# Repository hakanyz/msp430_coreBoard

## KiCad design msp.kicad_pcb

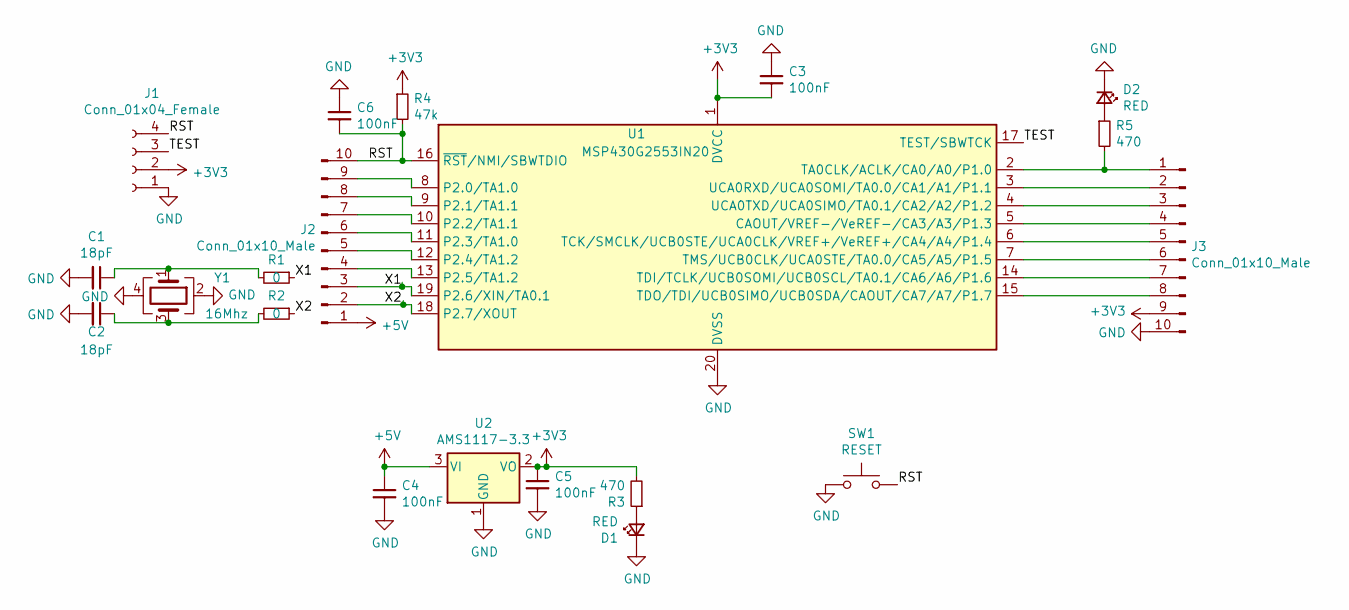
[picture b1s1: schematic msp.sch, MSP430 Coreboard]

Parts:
C1, C2: 18pF; C_0805_2012Metric
C3, C4, C5, C6: 100nF; C_0805_2012Metric
D1, D2: RED; LED_0805_2012Metric
J1: Conn_01x04_Female; PinSocket_1x04_P2.54mm_Vertical
J2, J3: Conn_01x10_Male; PinSocket_1x10_P2.54mm_Vertical
R1, R2: 0; R_0805_2012Metric
R3, R5: 470; R_0805_2012Metric
R4: 47k; R_0805_2012Metric
SW1: RESET; SW_Push_1P1T_NO_6x6mm_H9.5mm
U1: MSP430G2553IN20; TSSOP-20_4.4x6.5mm_P0.65mm
U2: AMS1117-3.3; SOT-223-3_TabPin2
Y1: 16Mhz; Crystal_SMD_3225-4Pin_3.2x2.5mm

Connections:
+3V3: C3.2, C5.1, J1.2, J3.9, R3.2, R4.1, U1.1 (DVCC), U2.2 (VO)
+5V: C4.1, J2.1, U2.3 (VI)
/RST: C6.2, J1.4, J2.10, R4.2, SW1.2, U1.16 (~RST~/NMI/SBWTDIO); also elsewhere on the board
/TEST: J1.3, U1.17 (TEST/SBWTCK)
/X1: J2.3, R1.1, U1.19 (P2.6/XIN/TA0.1)
/X2: J2.2, R2.1, U1.18 (P2.7/XOUT)
GND: C1.2, C2.2, C3.1, C4.2, C5.2, C6.1, D1.1 (K), D2.1 (K), J1.1, J3.10, SW1.1, U1.20 (DVSS), U2.1 (GND), Y1.2, Y1.4; also elsewhere on the board
unnamed: C1.1, R1.2, Y1.1
unnamed: C2.1, R2.2, Y1.3
unnamed: D1.2 (A), R3.1
unnamed: D2.2 (A), R5.1
unnamed: J2.4, U1.13 (P2.5/TA1.2)
unnamed: J2.5, U1.12 (P2.4/TA1.2)
unnamed: J2.6, U1.11 (P2.3/TA1.0)
unnamed: J2.7, U1.10 (P2.2/TA1.1)
unnamed: J2.8, U1.9 (P2.1/TA1.1)
unnamed: J2.9, U1.8 (P2.0/TA1.0)
unnamed: J3.1, R5.2, U1.2 (TA0CLK/ACLK/CA0/A0/P1.0)
unnamed: J3.2, U1.3 (UCA0RXD/UCA0SOMI/TA0.0/CA1/A1/P1.1)
unnamed: J3.3, U1.4 (UCA0TXD/UCA0SIMO/TA0.1/CA2/A2/P1.2)
unnamed: J3.4, U1.5 (CAOUT/VREF-/VeREF-/CA3/A3/P1.3)
unnamed: J3.5, U1.6 (TCK/SMCLK/UCB0STE/UCA0CLK/VREF+/VeREF+/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)
unnamed: J3.6, U1.7 (TMS/UCB0CLK/UCA0STE/TA0.0/CA5/A5/P1.5)
unnamed: J3.7, U1.14 (TDI/TCLK/UCB0SOMI/UCB0SCL/TA0.1/CA6/A6/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)
unnamed: J3.8, U1.15 (TDO/TDI/UCB0SIMO/UCB0SDA/CAOUT/CA7/A7/P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)

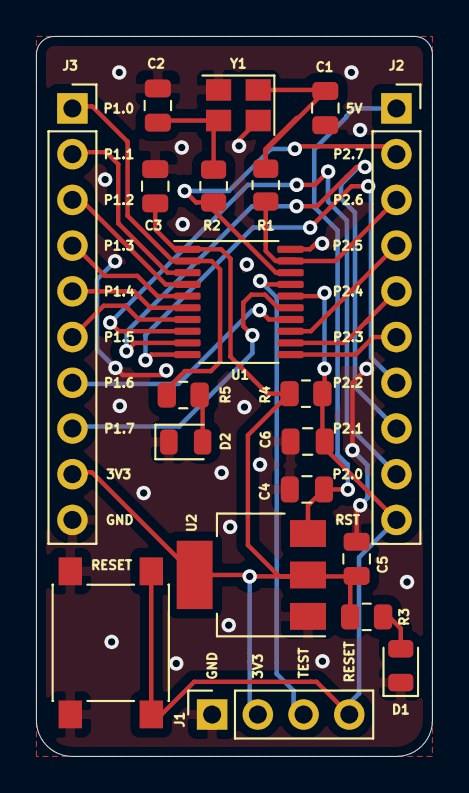
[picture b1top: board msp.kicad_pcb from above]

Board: 2 copper layers, 22.0 x 40.0 mm, 20 parts (0 on the bottom side), 25 nets.

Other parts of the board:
RESET: RESET; SW_Push_1P1T_NO_6x6mm_H9.5mm

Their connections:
/RST: RESET.2; also elsewhere on the board
GND: RESET.1; also elsewhere on the board

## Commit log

2021-12-06 Version 1
